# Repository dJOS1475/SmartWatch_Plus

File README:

The Tandy 1000 SmartWatch+ module adds a Clock & Calendar to your 1000. All you need to do is install it under the BIOS ROM and then use the Y2K Patched SMWCLOCK.COM utility to set the time automatically via your Autoexec.bat file.

I made this design because the original SmartWatch batteries are now mostly dead and can't be replaced. The 1000 SmartWatch+ uses a standard CR1632 Lithium coin cell for long life and easy replacement.

This HX/SX version should fit most Tandy 1000 machines (except the 1000 EX) but was designed for the HX and SX machines. If it physically fits in your 1000, it will work. it should also work in other PC Clones with a 28 Pin Bios ROM chip.

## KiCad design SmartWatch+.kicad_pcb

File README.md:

# SmartWatch_Plus
SmartWatch+ Tandy 1000 HX, SX etc Edition

The Tandy 1000 SmartWatch+ module adds a Clock & Calendar to your 1000. All you need to do is install it under the BIOS ROM and then use the Y2K Patched SMWCLOCK.COM utility to set the time automatically via your Autoexec.bat file.

I made this design because the original SmartWatch batteries are now mostly dead and can't be replaced. The 1000 SmartWatch+ uses a standard CR1632 Lithium coin cell for long life and easy replacement.

This HX/SX version should fit most Tandy 1000 machines (except the 1000 EX) but was designed for the HX and SX machines. If it physically fits in your 1000, it will work. it should also work in other PC Clones with a 28 Pin Bios ROM chip.

Y2K SmartWatch Software is here: https://www.dropbox.com/s/kctqpwzjxgymfz9/smwy2k.zip?dl=0

My Store can be found here: https://www.tindie.com/stores/CyberneticSys/

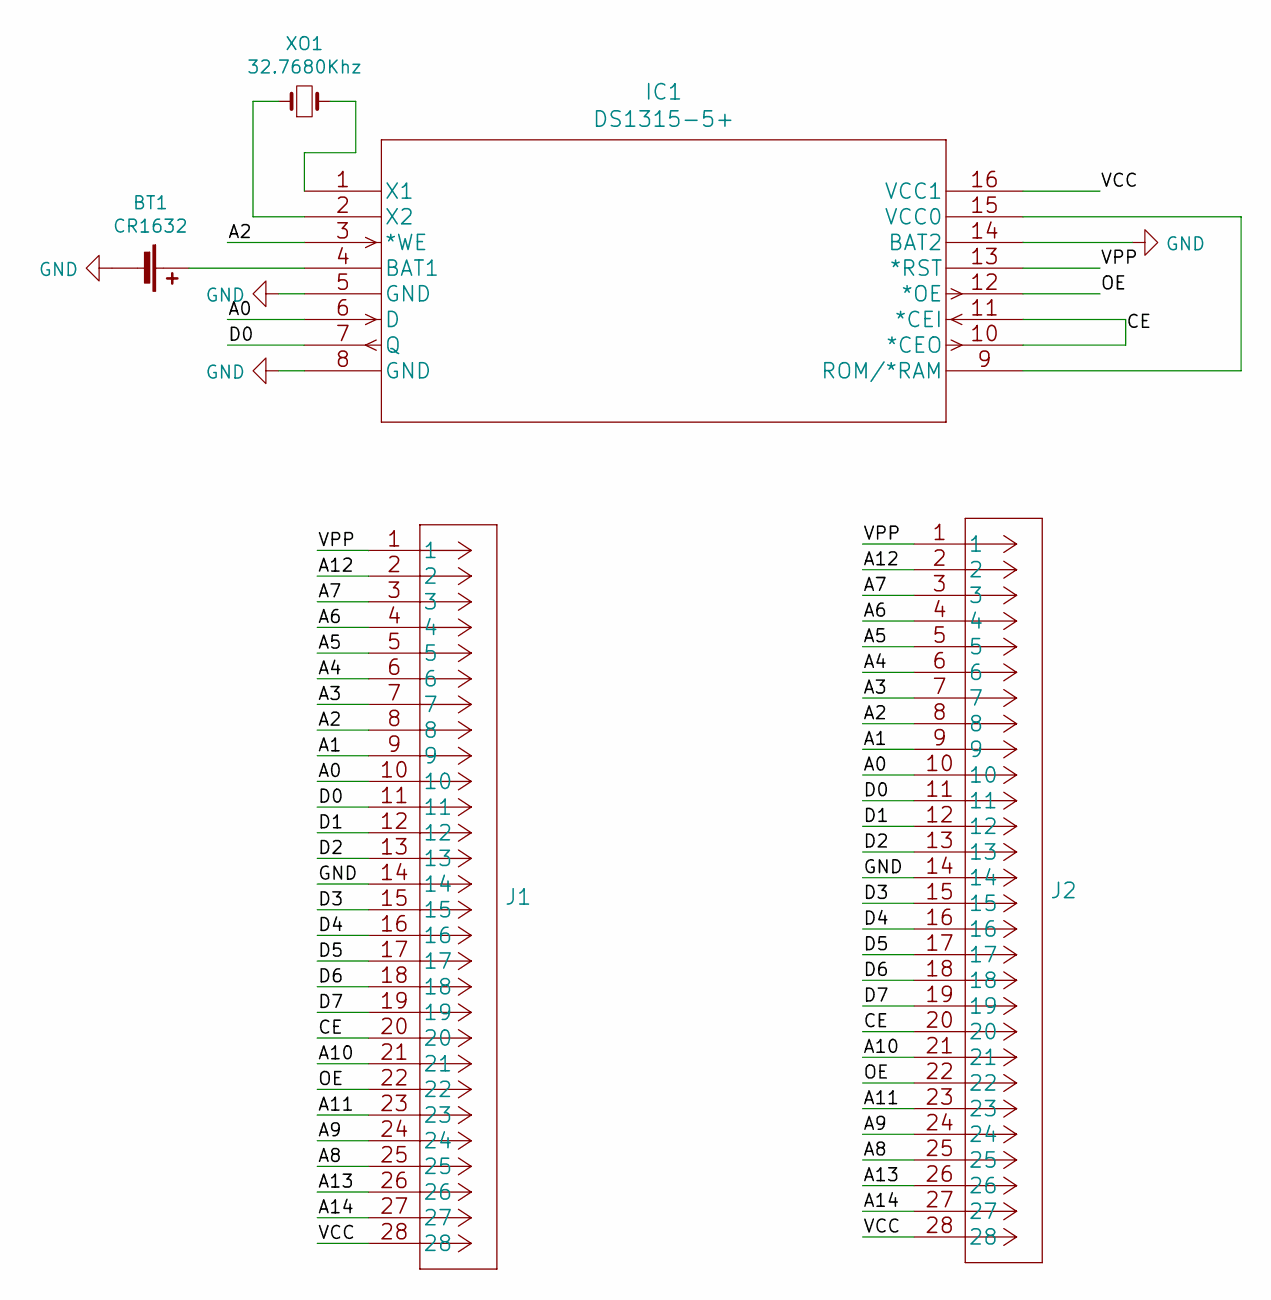
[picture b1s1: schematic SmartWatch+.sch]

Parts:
BT1: CR1632; BH600
IC1: DS1315-5+; DS1315-5&plus_
J1, J2: 2-1571586-9; DIP-28_600mil_SW
XO1: 32.7680Khz; TC26H

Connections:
/A0: IC1.6 (D), J1.10, J2.10
/A1: J1.9, J2.9
/A2: IC1.3 (*WE), J1.8, J2.8
/A3: J1.7, J2.7
/A4: J1.6, J2.6
/A5: J1.5, J2.5
/A6: J1.4, J2.4
/A7: J1.3, J2.3
/A8: J1.25, J2.25
/A9: J1.24, J2.24
/A10: J1.21, J2.21
/A11: J1.23, J2.23
/A12: J1.2, J2.2
/A13: J1.26, J2.26
/A14: J1.27, J2.27
/CE: IC1.10 (*CEO), IC1.11 (*CEI), J1.20, J2.20
/D0: IC1.7 (Q), J1.11, J2.11
/D1: J1.12, J2.12
/D2: J1.13, J2.13
/D3: J1.15, J2.15
/D4: J1.16, J2.16
/D5: J1.17, J2.17
/D6: J1.18, J2.18
/D7: J1.19, J2.19
/OE: IC1.12 (*OE), J1.22, J2.22
/VCC: IC1.16 (VCC1), J1.28, J2.28
/VPP: IC1.13 (*RST), J1.1, J2.1
GND: BT1.2 (-), IC1.5 (GND), IC1.8 (GND), IC1.14 (BAT2), J1.14, J2.14
unnamed: BT1.1 (+), IC1.4 (BAT1)
unnamed: IC1.1 (X1), XO1.2
unnamed: IC1.2 (X2), XO1.1
unnamed: IC1.9 (ROM/*RAM), IC1.15 (VCC0)

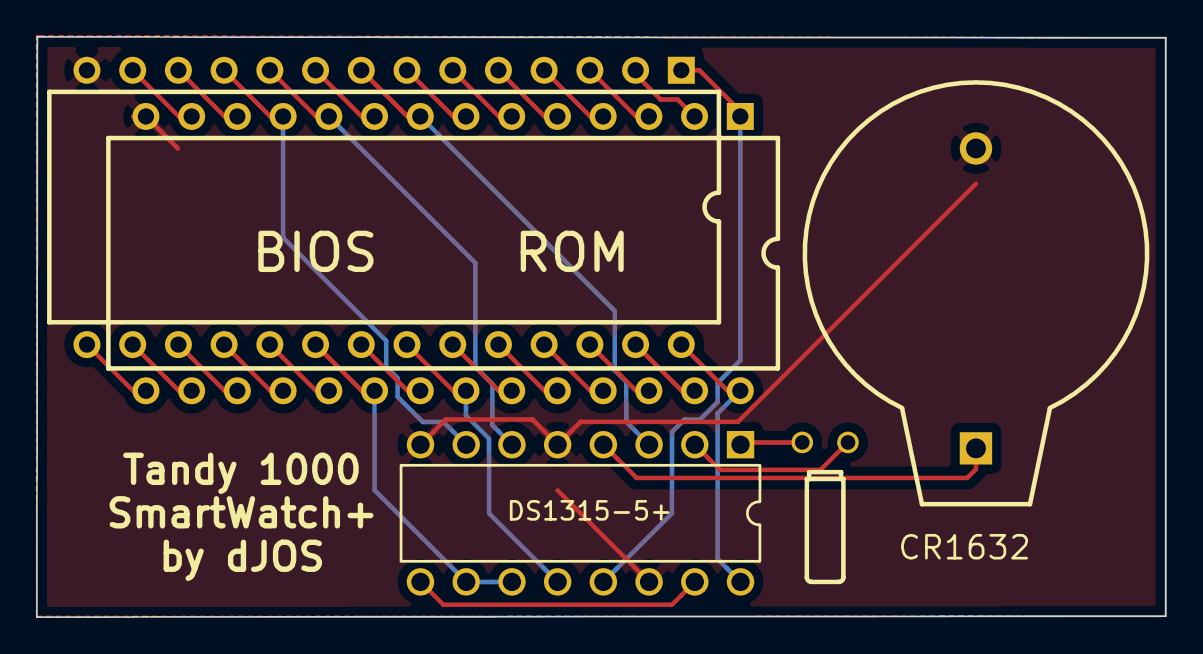
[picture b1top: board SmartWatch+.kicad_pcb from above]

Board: 2 copper layers, 62.7 x 32.2 mm, 5 parts (0 on the bottom side), 32 nets.

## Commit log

2020-05-18 Add files via upload
    Updated 28-pin Socket to have actual Pin Lables.
